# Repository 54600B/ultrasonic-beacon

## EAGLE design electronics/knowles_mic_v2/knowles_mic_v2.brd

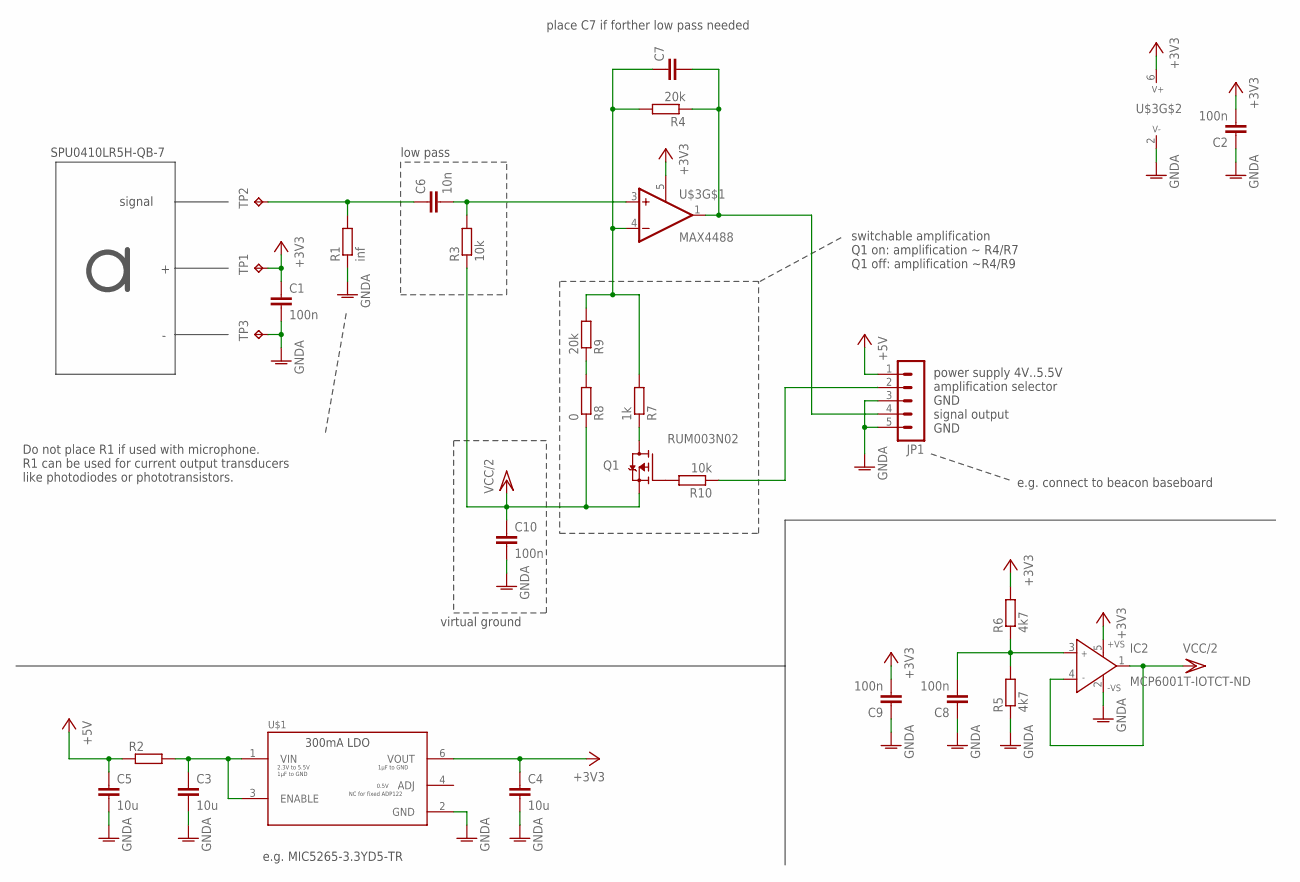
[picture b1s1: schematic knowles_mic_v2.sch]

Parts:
C1, C2, C8, C9, C10: 100n; C0603
C3, C4, C5: 10u; C0805
C6: 10n; C0603
C7: C-EUC0603; C0603
IC2: MCP6001T-IOTCT-ND; SOT23-5
JP1: PSS_5G; 22-23-2051
Q1: RUM003N02; SC75_INFINEON
R1: inf; R0603
R2: R-EU_R0603; R0603
R3, R10: 10k; R0603
R4, R9: 20k; R0603
R5, R6: 4k7; R0603
R7: 1k; R0603
R8: 0; R0603
TP1, TP2, TP3: TPTP06R; TP06R
U$1: ADP123; TSOT23-6
U$3: MAX4488; TSOT23-6

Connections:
+3V3: C1.1, C2.2, C4.1, C9.2, IC2.5 (+VS), R6.2, TP1.TP, U$1.6 (VOUT), U$3.5 (EN), U$3.6 (V+)
+5V: C5.1, JP1.1, R2.1
GNDA: C1.2, C2.1, C3.2, C4.2, C5.2, C8.1, C9.1, C10.2, IC2.2 (-VS), JP1.3, JP1.5, R1.1, R5.1, TP3.TP, U$1.2 (GND), U$3.2 (V-)
unnamed: C8.2, IC2.3 (IN+), R5.2, R6.1
unnamed: R8.2, R9.1
unnamed: C3.1, R2.2, U$1.1 (VIN), U$1.3 (ENABLE)
unnamed: JP1.2, R10.1
unnamed: Q1.1 (G), R10.2
unnamed: Q1.2 (D), R7.1
unnamed: C6.1, R1.2, TP2.TP
unnamed: C6.2, R3.2, U$3.3 (+IN)
unnamed: C7.2, JP1.4, R4.1, U$3.1 (OUT)
unnamed: C7.1, R4.2, R7.2, R9.2, U$3.4 (-IN)
VCC/2: C10.1, IC2.1 (OUT), IC2.4 (IN-), Q1.3 (S), R3.1, R8.1

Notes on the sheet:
e.g. MIC5265-3.3YD5-TR
signal
SPU0410LR5H-QB-7
Do not place R1 if used with microphone. R1 can be used for current output transducers like photodiodes or phototransistors.
low pass
place C7 if forther low pass needed
virtual ground
switchable amplification Q1 on: amplification ~ R4/R7 Q1 off: amplification ~R4/R9
power supply 4V..5.5V amplification selector GND signal output GND
e.g. connect to beacon baseboard

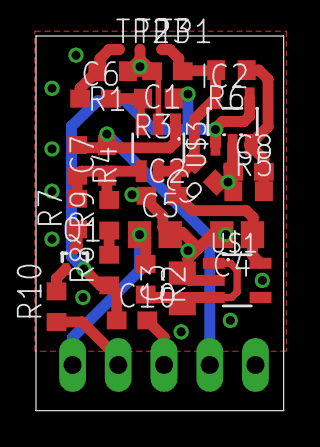
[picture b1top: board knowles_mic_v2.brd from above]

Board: 2 copper layers, 13.8 x 20.8 mm, 28 parts (1 on the bottom side), 14 nets.

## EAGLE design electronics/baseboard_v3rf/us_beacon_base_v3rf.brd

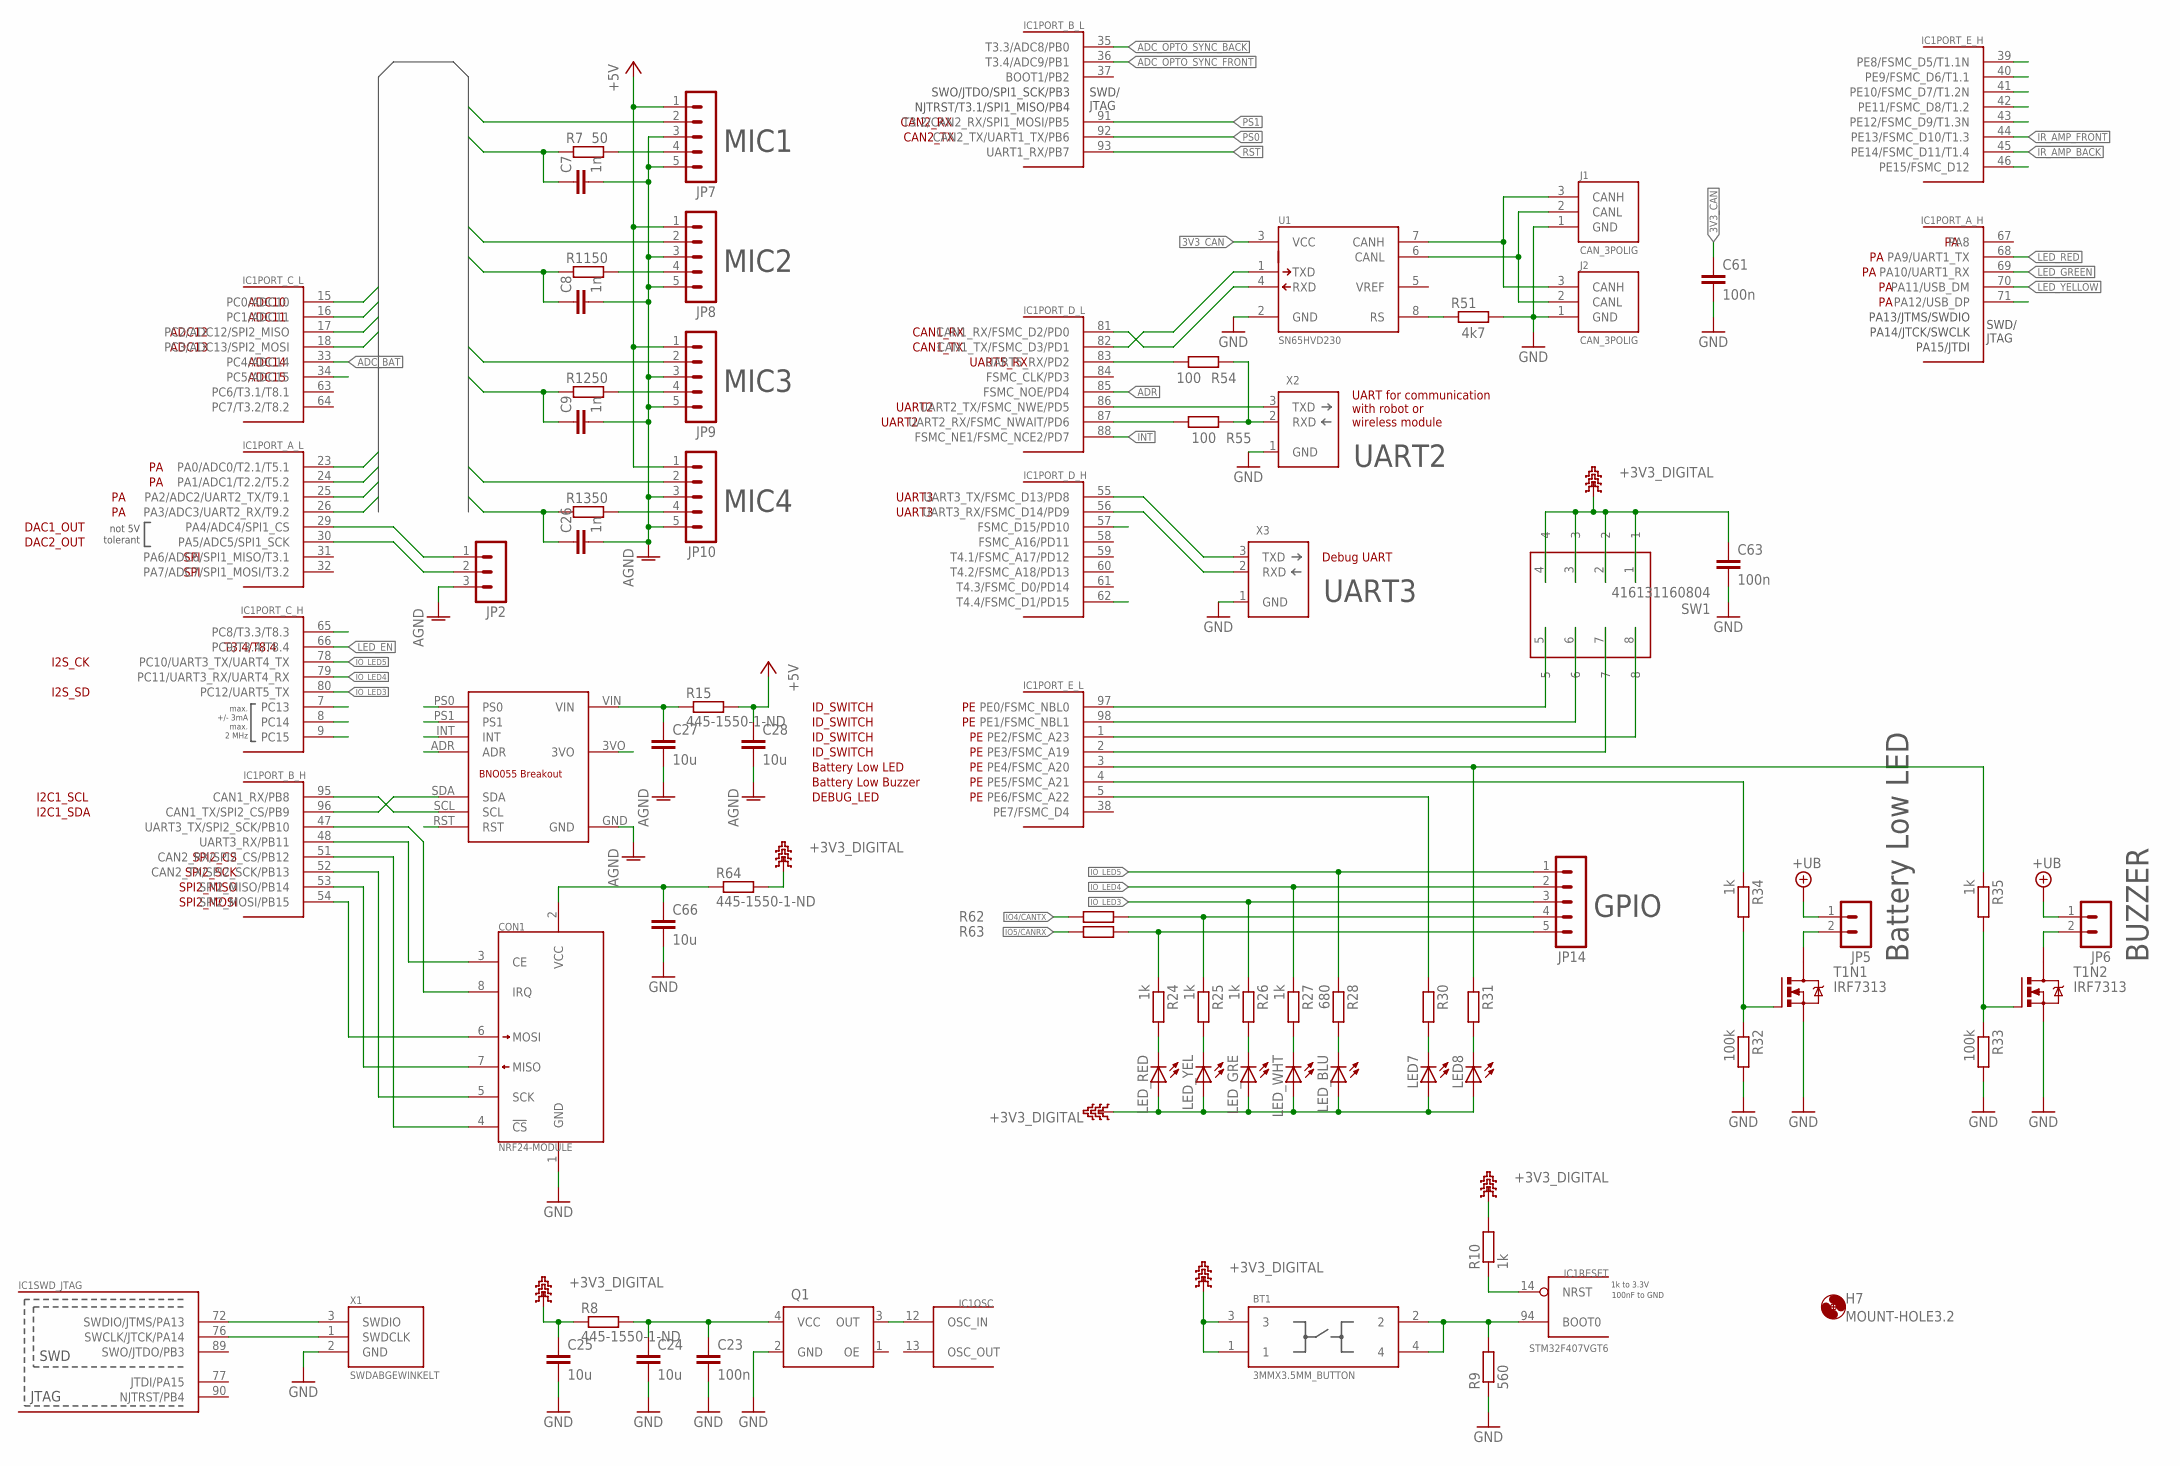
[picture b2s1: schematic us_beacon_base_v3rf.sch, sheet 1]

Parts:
BT1: 3MMX3.5MM_BUTTON
C7, C8, C9, C26: 1n; C0603
C23, C61, C63: 100n; C0603
C24, C25, C27, C28, C66: 10u; C0805
CON1: NRF24-MODULE
H7: MOUNT-HOLE3.2; 3,2
IC1: STM32F407VGT6; TQFP100
J1, J2: CAN_3POLIG; 7395-03
JP2: PSS_3G; 22-23-2031
JP5, JP6: PSS_2G; 22-23-2021
JP7, JP8, JP9, JP10, JP14: PSS_5G; 22-23-2051
LED7, LED8: LEDCHIP-LED0603; CHIP-LED0603
LED_BLU: LEDCHIP-LED0603; CHIP-LED0603
LED_GRE: LEDCHIP-LED0603; CHIP-LED0603
LED_RED: LEDCHIP-LED0603; CHIP-LED0603
LED_WHT: LEDCHIP-LED0603; CHIP-LED0603
LED_YEL: LEDCHIP-LED0603; CHIP-LED0603
Q1: XO53
R7, R11, R12, R13: 50; R0603
R8, R15, R64: 445-1550-1-ND; R0603
R9: 560; R0603
R10, R24, R25, R26, R27, R34, R35: 1k; R0603
R28: 680; R0603
R30, R31, R62, R63: R-EU_R0603; R0603
R32, R33: 100k; R0603
R51: 4k7; R0603
R54, R55: 100; R0603
SW1: 416131160804
T1: IRF7313; SO08
U1: SN65HVD230; SOIC-8
U$1: BNO055_ADAFRUIT_BREAKOUT; BNO055_BREAKOUT
X1: SWDABGEWINKELT; 7395-03
X2, X3: SERIAL_DEBUG_3PINL; 7395-03

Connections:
3V3_CAN: C61.1, U1.3 (VCC); also elsewhere on the board
+3V3_DIGITAL: BT1.1, BT1.3, C25.1, C63.1, LED7.A, LED8.A, LED_BLU.A, LED_GRE.A, LED_RED.A, LED_WHT.A, LED_YEL.A, R8.1, R10.2, R64.2, SW1.1, SW1.2, SW1.3, SW1.4; also elsewhere on the board
+5V: C28.1, JP7.1, JP8.1, JP9.1, JP10.1, R15.2; also elsewhere on the board
+UB: JP5.1, JP6.1; also elsewhere on the board
ADC_BAT: IC1.33 (PC4/ADC14); also elsewhere on the board
ADC_OPTO_SYNC_BACK: IC1.35 (T3.3/ADC8/PB0); also elsewhere on the board
ADC_OPTO_SYNC_FRONT: IC1.36 (T3.4/ADC9/PB1); also elsewhere on the board
ADR: IC1.85 (FSMC_NOE/PD4), U$1.ADR
AMP1: IC1.23 (PA0/ADC0/T2.1/T5.1), JP7.2
AMP2: IC1.24 (PA1/ADC1/T2.2/T5.2), JP8.2
AMP3: IC1.25 (PA2/ADC2/UART2_TX/T9.1), JP9.2
AMP4: IC1.26 (PA3/ADC3/UART2_RX/T9.2), JP10.2
DAC1/I2S1_WS: IC1.29 (PA4/ADC4/SPI1_CS), JP2.1
DAC2/SPI1_SCK: IC1.30 (PA5/ADC5/SPI1_SCK), JP2.2
GND: C7.2, C8.2, C9.2, C23.2, C24.2, C25.2, C26.2, C27.2, C28.2, C61.2, C63.2, C66.2, CON1.1 (GND), J1.1 (GND), J2.1 (GND), JP2.3, JP7.3, JP7.5, JP8.3, JP8.5, JP9.3, JP9.5, JP10.3, JP10.5, Q1.2 (GND), R9.1, R32.2, R33.2, R51.2, T1.1 (S), T1.3 (S), U1.2 (GND), U$1.GND, X1.2 (GND), X2.1 (GND), X3.1 (GND); also elsewhere on the board
INT: IC1.88 (FSMC_NE1/FSMC_NCE2/PD7), U$1.INT
IO4: JP14.4, R25.1, R62.2
IO4/CANTX: IC1.82 (CAN1_TX/FSMC_D3/PD1), R62.1, U1.1 (TXD)
IO5: JP14.5, R24.1, R63.2
IO5/CANRX: IC1.81 (CAN1_RX/FSMC_D2/PD0), R63.1, U1.4 (RXD)
IO_LED3: IC1.80 (PC12/UART5_TX), JP14.3, R26.1
IO_LED4: IC1.79 (PC11/UART3_RX/UART4_RX), JP14.2, R27.1
IO_LED5: IC1.78 (PC10/UART3_TX/UART4_TX), JP14.1, R28.1
IR_AMP_BACK: IC1.45 (PE14/FSMC_D11/T1.4); also elsewhere on the board
IR_AMP_FRONT: IC1.44 (PE13/FSMC_D10/T1.3); also elsewhere on the board
LED_EN: IC1.66 (PC9/T3.4/T8.4); also elsewhere on the board
LED_GREEN: IC1.69 (PA10/UART1_RX); also elsewhere on the board
LED_RED: IC1.68 (PA9/UART1_TX); also elsewhere on the board
LED_YELLOW: IC1.70 (PA11/USB_DM); also elsewhere on the board
MIC1: C7.1, IC1.15 (PC0/ADC10), R7.1
MIC2: C8.1, IC1.16 (PC1/ADC11), R11.1
MIC3: C9.1, IC1.17 (PC2/ADC12/SPI2_MISO), R12.1
MIC4: C26.1, IC1.18 (PC3/ADC13/SPI2_MOSI), R13.1
unnamed: IC1.72 (SWDIO/JTMS/PA13), X1.3 (SWDIO)
unnamed: IC1.76 (SWCLK/JTCK/PA14), X1.1 (SWDCLK)
unnamed: JP7.4, R7.2
unnamed: IC1.12 (OSC_IN), Q1.3 (OUT)
unnamed: C23.1, C24.1, Q1.4 (VCC), R8.2
unnamed: JP9.4, R12.2
unnamed: IC1.14 (NRST), R10.1
unnamed: JP8.4, R11.2
unnamed: JP10.4, R13.2
unnamed: BT1.2, BT1.4, IC1.94 (BOOT0), R9.2
unnamed: IC1.83 (UART5_RX/PD2), R54.1
unnamed: C27.1, R15.1, U$1.VIN
unnamed: R54.2, R55.2, X2.2 (RXD)
unnamed: IC1.95 (CAN1_RX/PB8), U$1.SCL
unnamed: IC1.96 (CAN1_TX/SPI2_CS/PB9), U$1.SDA
unnamed: IC1.86 (UART2_TX/FSMC_NWE/PD5), X2.3 (TXD)
unnamed: IC1.87 (UART2_RX/FSMC_NWAIT/PD6), R55.1
unnamed: IC1.55 (UART3_TX/FSMC_D13/PD8), X3.3 (TXD)
unnamed: IC1.56 (UART3_RX/FSMC_D14/PD9), X3.2 (RXD)
unnamed: LED_RED.C, R24.2
unnamed: LED_YEL.C, R25.2
unnamed: LED_GRE.C, R26.2
unnamed: LED_WHT.C, R27.2
unnamed: LED_BLU.C, R28.2
unnamed: LED7.C, R30.2
unnamed: LED8.C, R31.2
unnamed: IC1.3 (PE4/FSMC_A20), R31.1, R35.1
unnamed: IC1.5 (PE6/FSMC_A22), R30.1
unnamed: R32.1, R34.2, T1.2 (G)
unnamed: R33.1, R35.2, T1.4 (G)
unnamed: JP5.2, T1.7 (D)
unnamed: IC1.4 (PE5/FSMC_A21), R34.1
unnamed: JP6.2, T1.5 (D)
unnamed: IC1.2 (PE3/FSMC_A19), SW1.7
unnamed: IC1.97 (PE0/FSMC_NBL0), SW1.5
unnamed: IC1.98 (PE1/FSMC_NBL1), SW1.6
unnamed: IC1.1 (PE2/FSMC_A23), SW1.8
unnamed: R51.1, U1.8 (RS)
unnamed: J1.3 (CANH), J2.3 (CANH), U1.7 (CANH)
unnamed: J1.2 (CANL), J2.2 (CANL), U1.6 (CANL)
unnamed: CON1.4 (!CS), IC1.51 (CAN2_RX/SPI2_CS/PB12)
unnamed: CON1.5 (SCK), IC1.52 (CAN2_TX/SPI2_SCK/PB13)
unnamed: CON1.7 (MISO), IC1.53 (SPI2_MISO/PB14)
unnamed: CON1.6 (MOSI), IC1.54 (SPI2_MOSI/PB15)
unnamed: CON1.3 (CE), IC1.48 (UART3_RX/PB11)
unnamed: CON1.8 (IRQ), IC1.47 (UART3_TX/SPI2_SCK/PB10)
unnamed: C66.1, CON1.2 (VCC), R64.1
PS0: IC1.92 (CAN2_TX/UART1_TX/PB6), U$1.PS0
PS1: IC1.91 (T3.2/CAN2_RX/SPI1_MOSI/PB5), U$1.PS1
RST: IC1.93 (UART1_RX/PB7), U$1.RST
VBAT: IC1.6 (VBAT)

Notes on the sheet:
ADC11
SPI2_CS
SPI2_SCK
CAN1_RX
CAN1_TX
SPI2_MOSI
SPI2_MISO
ADC10
ADC14
ADC15
UART2
UART3
DAC1_OUT
DAC2_OUT
I2S_CK
I2S_SD
SPI
CAN2_RX
CAN2_TX
I2C1_SCL
I2C1_SDA
ADC12
ADC13
ID_SWITCH
Battery Low LED
Battery Low Buzzer
DEBUG_LED
MIC1
MIC2
MIC3
MIC4
GPIO
BUZZER
Debug UART
UART for communication with robot or wireless module
T3.4/T8.4
UART5_RX

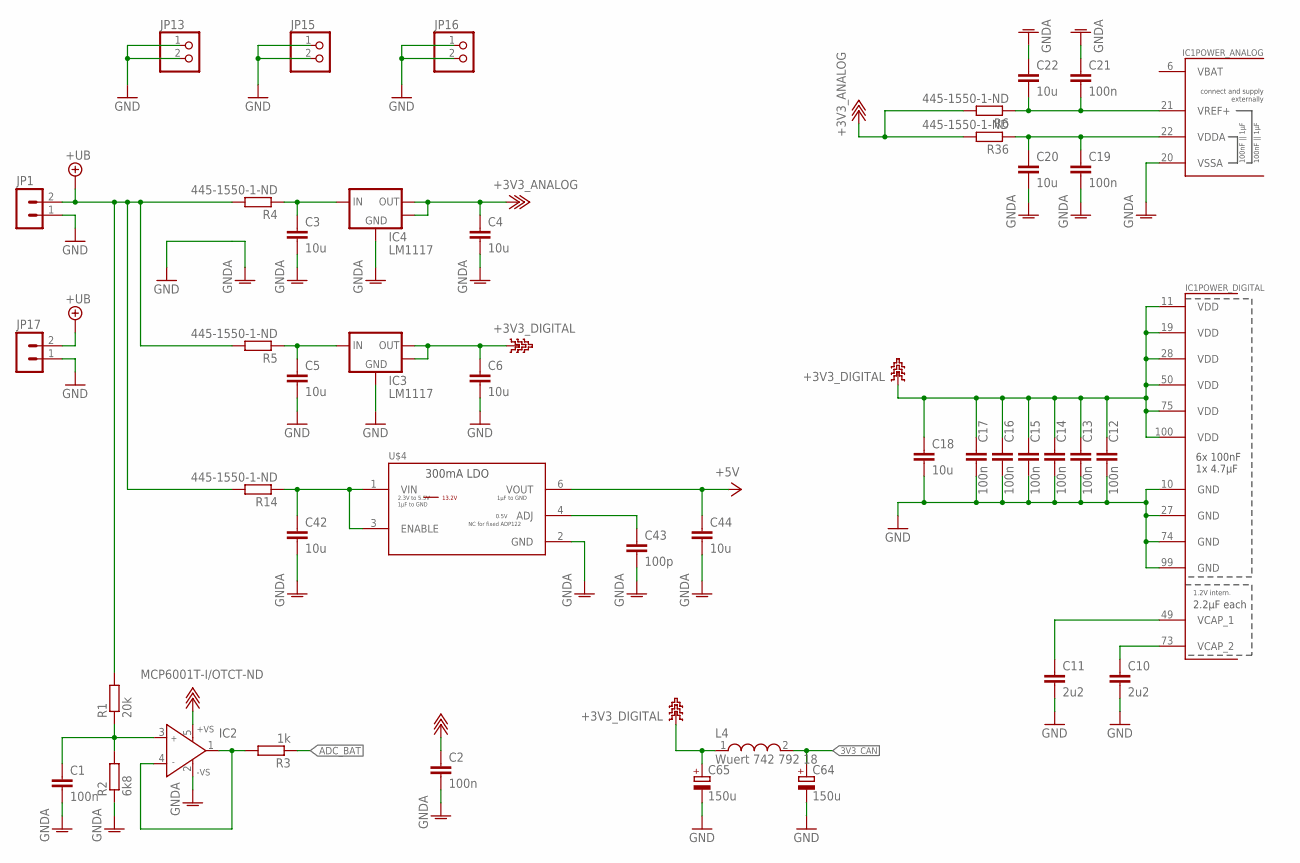
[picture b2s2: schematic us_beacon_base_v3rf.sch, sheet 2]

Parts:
C1, C2, C12, C13, C14, C15, C16, C17, C19, C21: 100n; C0603
C3, C4, C5, C6, C18, C20, C22, C42, C44: 10u; C0805
C10, C11: 2u2; C0805
C43: 100p; C0603
C64, C65: 150u; E3,5-8
IC1: STM32F407VGT6; TQFP100
IC2: MCP6001T-I/OTCT-ND; SOT23-5
IC3, IC4: LM1117; SOT223
JP1, JP17: PSS_2G; 22-23-2021
JP13, JP15, JP16: PINHD-1X2; 1X02
L4: Wuert 742 792 18; WE-CBF_1206(W=5.2)
R1: 20k; R0603
R2: 6k8; R0603
R3: 1k; R0603
R4, R5, R6, R14, R36: 445-1550-1-ND; R0603
U$4: AP2210K-5.0; TSOT23-6

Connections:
3V3_CAN: C64.+, L4.2; also elsewhere on the board
+3V3_ANALOG: C2.1, C4.1, IC2.5 (+VS), IC4.2 (OUT), IC4.4 (OUT), R6.2, R36.2; also elsewhere on the board
+3V3_DIGITAL: C6.1, C12.1, C13.1, C14.1, C15.1, C16.1, C17.1, C18.1, C65.+, IC1.11 (VDD), IC1.19 (VDD), IC1.28 (VDD), IC1.50 (VDD), IC1.75 (VDD), IC1.100 (VDD), IC3.2 (OUT), IC3.4 (OUT), L4.1; also elsewhere on the board
+5V: C44.1, U$4.6 (VOUT); also elsewhere on the board
+UB: JP1.2, JP17.2, R1.2, R4.2, R5.2, R14.2; also elsewhere on the board
ADC_BAT: R3.1; also elsewhere on the board
GND: C1.2, C2.2, C3.2, C4.2, C5.2, C6.2, C10.2, C11.2, C12.2, C13.2, C14.2, C15.2, C16.2, C17.2, C18.2, C19.2, C20.2, C21.1, C22.1, C42.2, C43.2, C44.2, C64.-, C65.-, IC1.10 (GND), IC1.20 (VSSA), IC1.27 (GND), IC1.74 (GND), IC1.99 (GND), IC2.2 (-VS), IC3.1 (GND), IC4.1 (GND), JP1.1, JP13.1, JP13.2, JP15.1, JP15.2, JP16.1, JP16.2, JP17.1, R2.1, U$4.2 (GND); also elsewhere on the board
unnamed: IC2.1 (OUT), IC2.4 (IN-), R3.2
unnamed: C1.1, IC2.3 (IN+), R1.1, R2.2
unnamed: C42.1, R14.1, U$4.1 (VIN), U$4.3 (ENABLE)
unnamed: C3.1, IC4.3 (IN), R4.1
unnamed: C10.1, IC1.73 (VCAP_2)
unnamed: C5.1, IC3.3 (IN), R5.1
unnamed: C11.1, IC1.49 (VCAP_1)
unnamed: C21.2, C22.2, IC1.21 (VREF+), R6.1
unnamed: C43.1, U$4.4 (ADJ)
unnamed: C19.1, C20.1, IC1.22 (VDDA), R36.1
VBAT: IC1.6 (VBAT)

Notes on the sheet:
13.2V

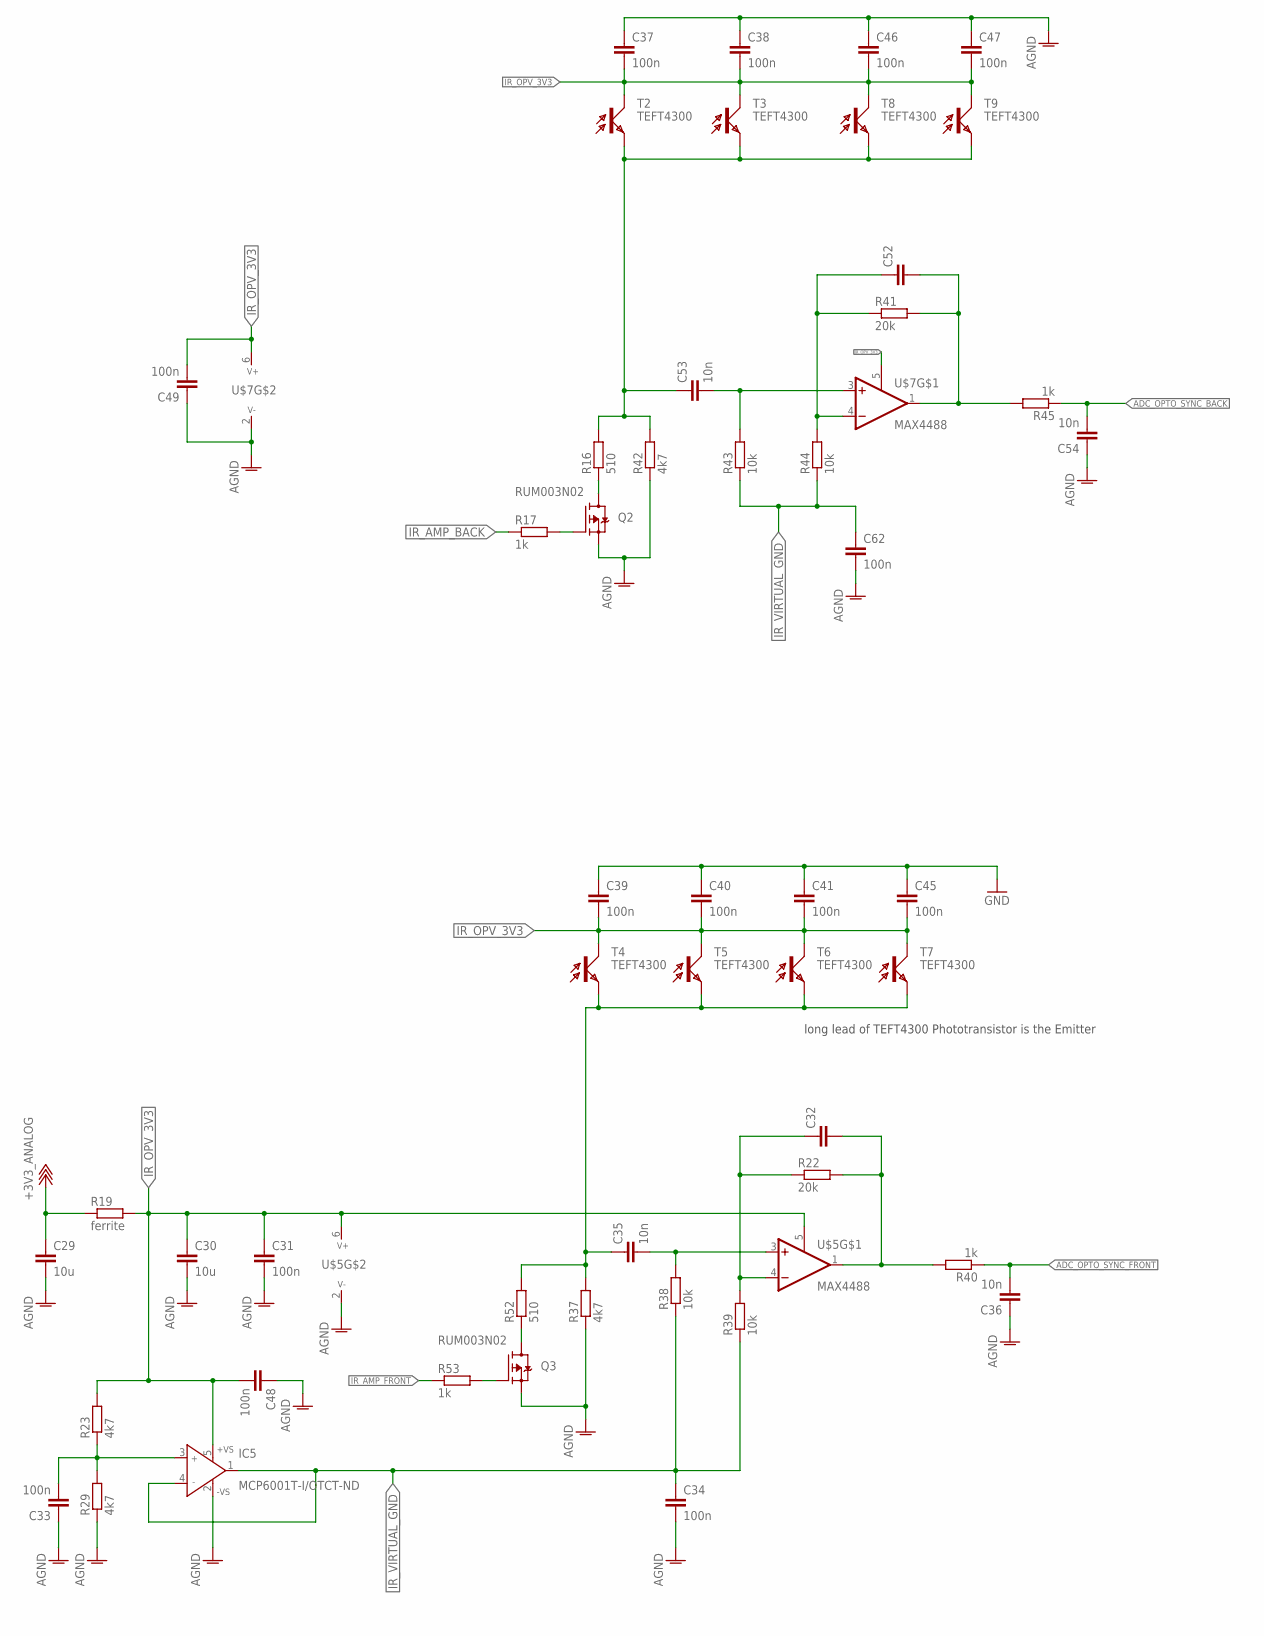
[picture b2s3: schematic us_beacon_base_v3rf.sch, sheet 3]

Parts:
C29, C30: 10u; C0805
C31, C33, C34, C37, C38, C39, C40, C41, C45, C46, C47, C48, C49, C62: 100n; C0603
C32, C52: C-EUC0603; C0603
C35, C36, C53, C54: 10n; C0603
IC5: MCP6001T-I/OTCT-ND; SOT23-5
Q2, Q3: RUM003N02; SC75_INFINEON
R16, R52: 510; R0603
R17, R40, R45, R53: 1k; R0603
R19: ferrite; R0603
R22, R41: 20k; R0603
R23, R29, R37, R42: 4k7; R0603
R38, R39, R43, R44: 10k; R0603
T2, T3, T4, T5, T6, T7, T8, T9: TEFT4300; LPT80A
U$5, U$7: MAX4488; TSOT23-6

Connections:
+3V3_ANALOG: C29.1, R19.1; also elsewhere on the board
ADC_OPTO_SYNC_BACK: C54.2, R45.1; also elsewhere on the board
ADC_OPTO_SYNC_FRONT: C36.2, R40.1; also elsewhere on the board
GND: C29.2, C30.2, C31.2, C33.1, C34.2, C36.1, C37.1, C38.1, C39.1, C40.1, C41.1, C45.1, C46.1, C47.1, C48.1, C49.1, C54.1, C62.2, IC5.2 (-VS), Q2.3 (S), Q3.3 (S), R29.1, R37.1, R42.1, U$5.2 (V-), U$7.2 (V-); also elsewhere on the board
IR_AMP_BACK: R17.1; also elsewhere on the board
IR_AMP_FRONT: R53.1; also elsewhere on the board
IR_OPV_3V3: C30.1, C31.1, C37.2, C38.2, C39.2, C40.2, C41.2, C45.2, C46.2, C47.2, C48.2, C49.2, IC5.5 (+VS), R19.2, R23.2, T2.C, T3.C, T4.C, T5.C, T6.C, T7.C, T8.C, T9.C, U$5.5 (EN), U$5.6 (V+), U$7.5 (EN), U$7.6 (V+)
IR_VIRTUAL_GND: C34.1, C62.1, IC5.1 (OUT), IC5.4 (IN-), R38.1, R39.1, R43.1, R44.1
unnamed: Q2.2 (D), R16.1
unnamed: Q2.1 (G), R17.2
unnamed: C53.1, R16.2, R42.2, T2.E, T3.E, T8.E, T9.E
unnamed: C35.2, R38.2, U$5.3 (+IN)
unnamed: Q3.2 (D), R52.1
unnamed: C32.2, R22.2, R40.2, U$5.1 (OUT)
unnamed: C32.1, R22.1, R39.2, U$5.4 (-IN)
unnamed: Q3.1 (G), R53.2
unnamed: C33.2, IC5.3 (IN+), R23.1, R29.2
unnamed: C52.2, R41.2, R45.2, U$7.1 (OUT)
unnamed: C52.1, R41.1, R44.2, U$7.4 (-IN)
unnamed: C35.1, R37.2, R52.2, T4.E, T5.E, T6.E, T7.E
unnamed: C53.2, R43.2, U$7.3 (+IN)

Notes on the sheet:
long lead of TEFT4300 Phototransistor is the Emitter

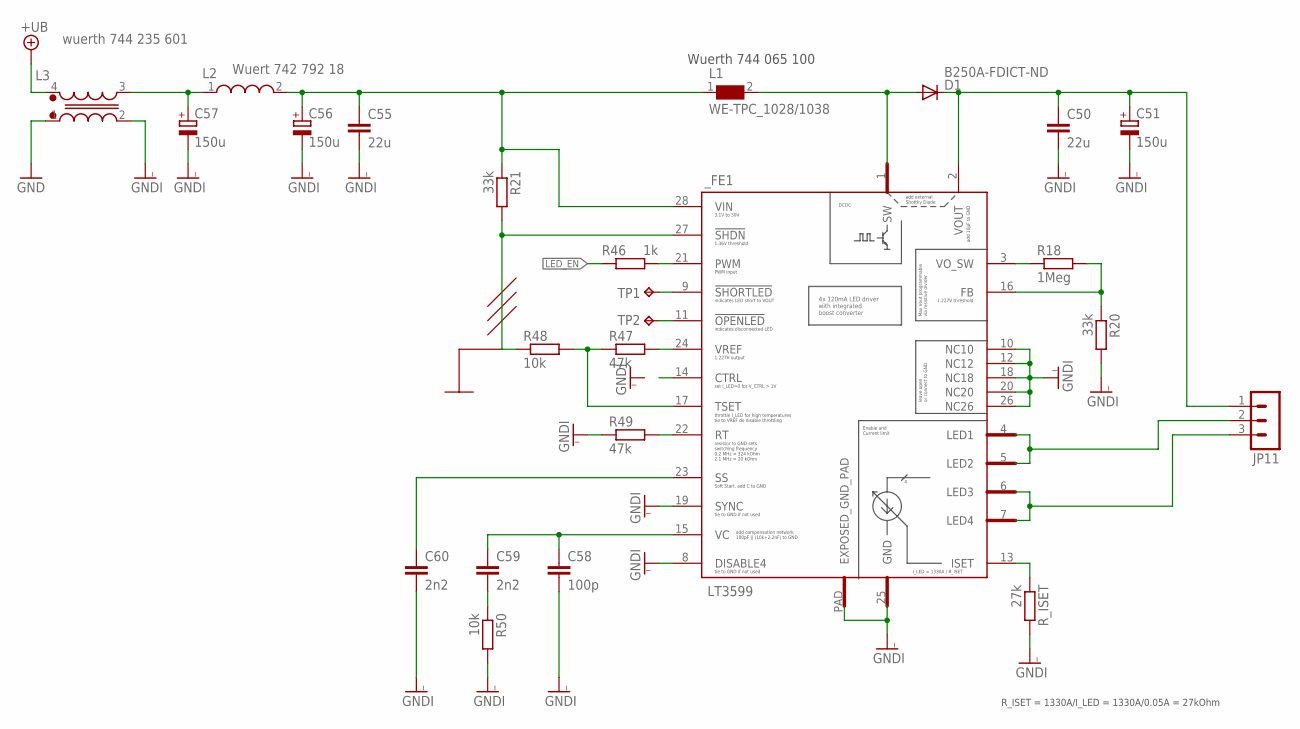
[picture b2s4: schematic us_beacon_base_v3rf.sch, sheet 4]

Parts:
C50, C55: 22u; C1206
C51, C56, C57: 150u; E3,5-8
C58: 100p; C0603
C59, C60: 2n2; C0603
D1: B250A-FDICT-ND; SMB
JP11: PSS_3G; 22-23-2031
L1: WE-TPC_1028/1038
L2: Wuert 742 792 18; WE-CBF_1206(W=5.2)
L3: wuerth 744 235 601; WE-CNSW_1812
R18: 1Meg; R0603
R20, R21: 33k; R0603
R46: 1k; R0603
R47, R49: 47k; R0603
R48, R50: 10k; R0603
R_ISET: 27k; R0603
TP1, TP2: TPTP06R; TP06R
_FE1: LT3599; TSSOP28

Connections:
+UB: L3.4 (1); also elsewhere on the board
DCDC_SW_NODE: D1.A, L1.2, _FE1.1 (SW)
GND: L3.1 (4); also elsewhere on the board
GNDI: C50.2, C51.-, C55.2, C56.-, C57.-, C58.2, C60.2, L3.2 (3), R20.2, R49.1, R50.2, R_ISET.2, _FE1.8 (DISABLE4), _FE1.10 (NC10), _FE1.12 (NC12), _FE1.18 (NC18), _FE1.19 (SYNC), _FE1.20 (NC20), _FE1.25 (GND), _FE1.26 (NC26), _FE1.PAD (EXPOSED_GND_PAD)
LED_EN: R46.1; also elsewhere on the board
unnamed: R46.2, _FE1.21 (PWM)
unnamed: C57.+, L2.1, L3.3 (2)
unnamed: C58.1, C59.1, _FE1.15 (VC)
unnamed: C50.1, C51.+, D1.C, JP11.1, _FE1.2 (VOUT)
unnamed: JP11.2, _FE1.4 (LED1), _FE1.5 (LED2)
unnamed: JP11.3, _FE1.6 (LED3), _FE1.7 (LED4)
unnamed: R18.2, R20.1, _FE1.16 (FB)
unnamed: R18.1, _FE1.3 (VO_SW)
unnamed: TP1.TP, _FE1.9 (!SHORTLED)
unnamed: TP2.TP, _FE1.11 (!OPENLED)
unnamed: R47.1, R48.2, _FE1.17 (TSET)
unnamed: R47.2, _FE1.24 (VREF)
unnamed: R21.2, R48.1, _FE1.27 (!SHDN)
unnamed: C55.1, C56.+, L1.1, L2.2, R21.1, _FE1.28 (VIN)
unnamed: R49.2, _FE1.22 (RT)
unnamed: C60.1, _FE1.23 (SS)
unnamed: C59.2, R50.1
unnamed: R_ISET.1, _FE1.13 (ISET)

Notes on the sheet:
R_ISET = 1330A/I_LED = 1330A/0.05A = 27kOhm
Wuerth 744 065 100

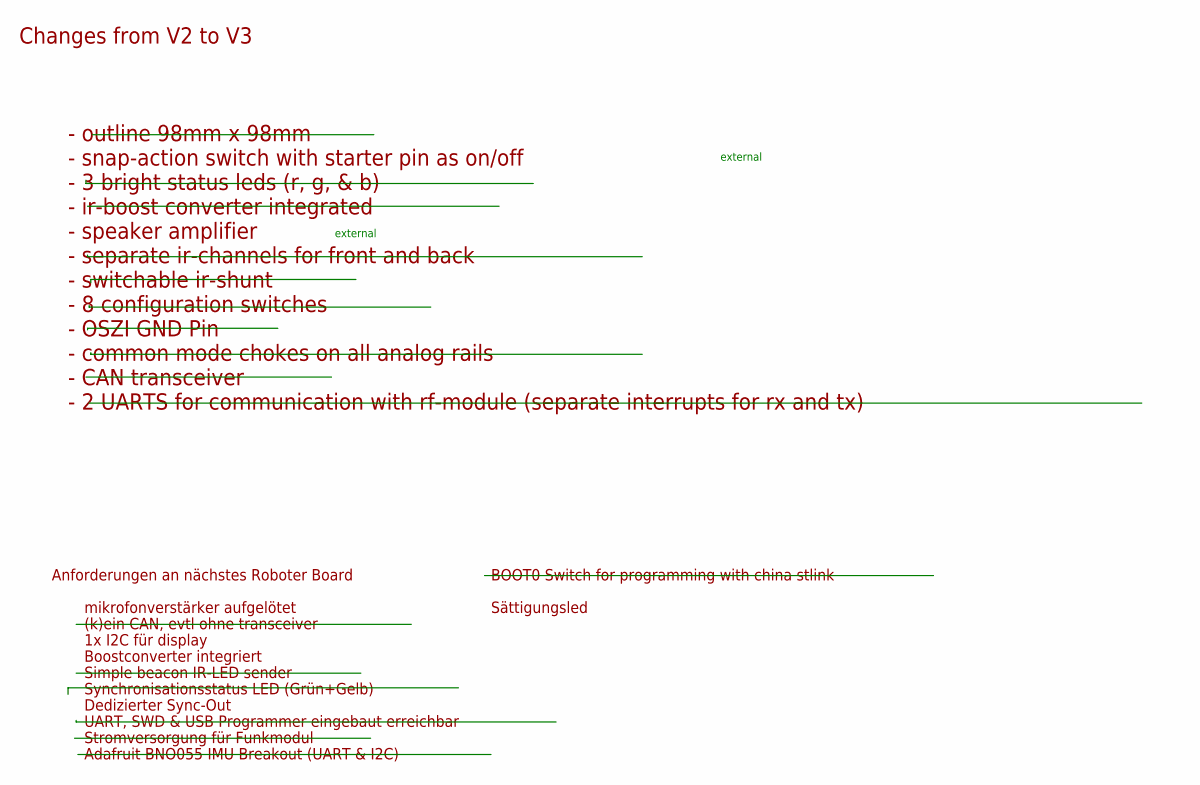
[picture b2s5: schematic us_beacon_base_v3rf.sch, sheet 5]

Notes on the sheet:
- outline 98mm x 98mm - snap-action switch with starter pin as on/off - 3 bright status leds (r, g, & b) - ir-boost converter integrated - speaker amplifier - separate ir-channels for front and back - switchable ir-shunt - 8 configuration switches - OSZI GND Pin - common mode chokes on all analog r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
Changes from V2 to V3
BOOT0 Switch for programming with china stlink
Sättigungsled
Anforderungen an nächstes Roboter Board
mikrofonverstärker aufgelötet
(k)ein CAN, evtl ohne transceiver
1x I2C für display
Boostconverter integriert
Simple beacon IR-LED sender
Synchronisationsstatus LED (Grün+Gelb)
Dedizierter Sync-Out
UART, SWD & USB Programmer eingebaut erreichbar
Stromversorgung für Funkmodul
Adafruit BNO055 IMU Breakout (UART & I2C)
external

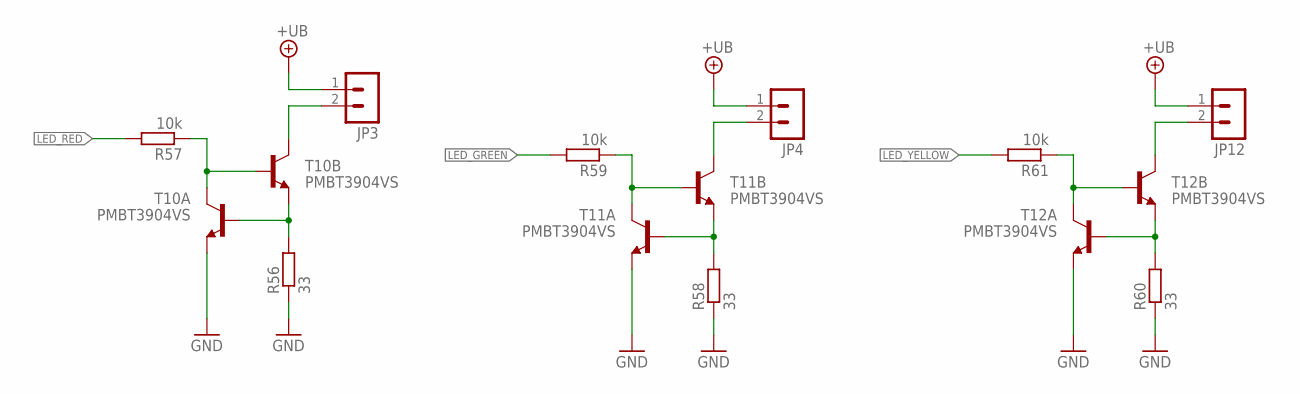
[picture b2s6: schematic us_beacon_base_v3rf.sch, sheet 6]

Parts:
JP3, JP4, JP12: PSS_2G; 22-23-2021
R56, R58, R60: 33; R0603
R57, R59, R61: 10k; R0603
T10, T11, T12: PMBT3904VS; SOT563

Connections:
+UB: JP3.1, JP4.1, JP12.1; also elsewhere on the board
GND: R56.1, R58.1, R60.1, T10.1 (E), T11.1 (E), T12.1 (E); also elsewhere on the board
LED_GREEN: R59.2; also elsewhere on the board
LED_RED: R57.2; also elsewhere on the board
LED_YELLOW: R61.2; also elsewhere on the board
unnamed: R56.2, T10.2 (B), T10.4 (E)
unnamed: R57.1, T10.5 (B), T10.6 (C)
unnamed: JP3.2, T10.3 (C)
unnamed: R58.2, T11.2 (B), T11.4 (E)
unnamed: R59.1, T11.5 (B), T11.6 (C)
unnamed: JP4.2, T11.3 (C)
unnamed: R60.2, T12.2 (B), T12.4 (E)
unnamed: R61.1, T12.5 (B), T12.6 (C)
unnamed: JP12.2, T12.3 (C)

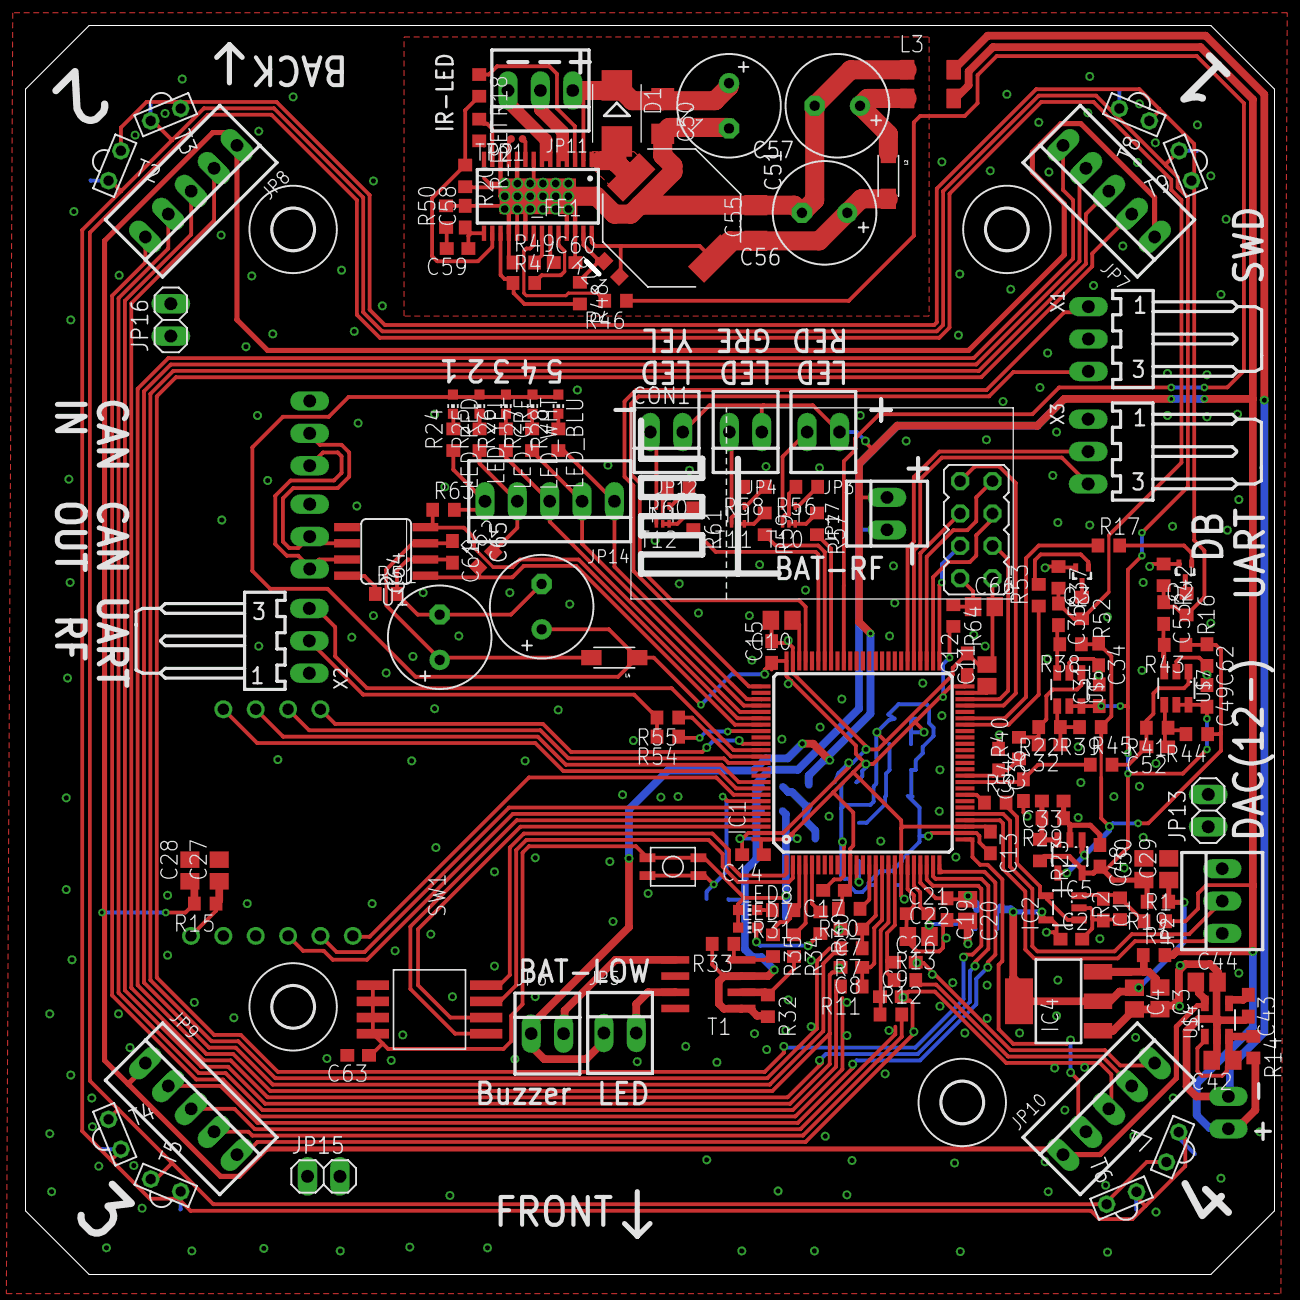
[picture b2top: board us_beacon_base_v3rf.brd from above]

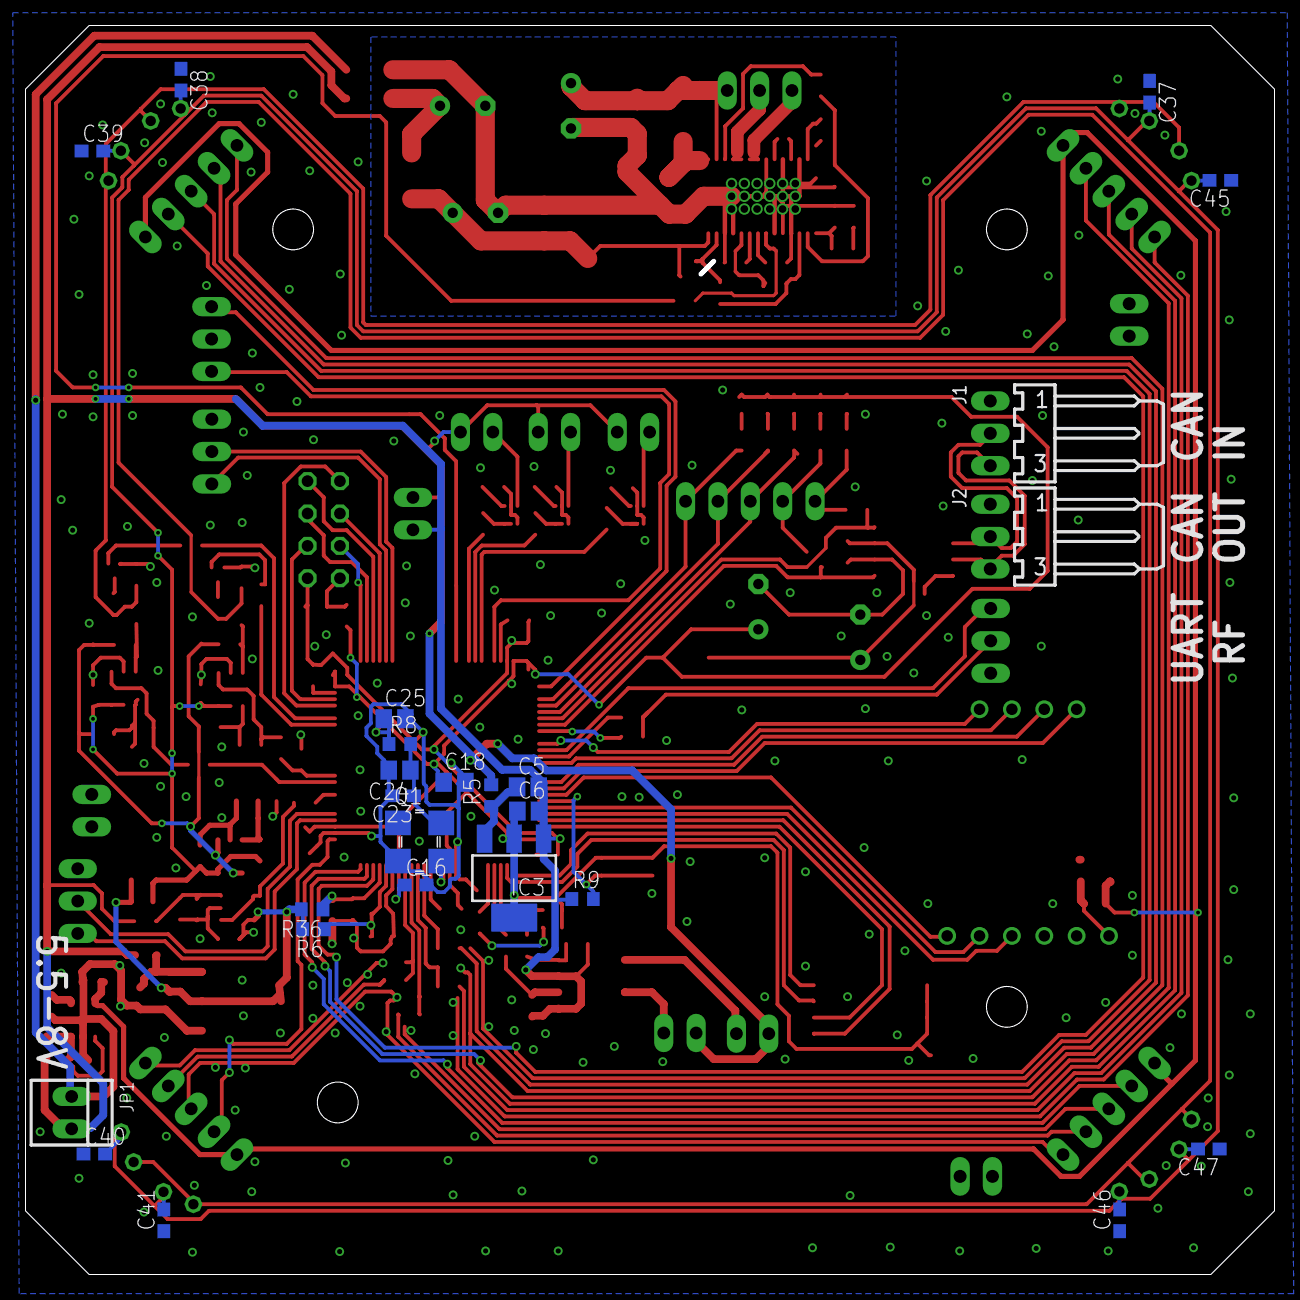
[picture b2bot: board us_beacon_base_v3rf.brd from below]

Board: 2 copper layers, 97.6 x 97.6 mm, 200 parts (25 on the bottom side), 138 nets.

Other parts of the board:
H5, H6, H8: MOUNT-HOLE3.2; 3,2

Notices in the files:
software/beacon-uC/US_Beacon_V3/Src/main.c:
Copyright (c) 2018 STMicroelectronics International N.V.
All rights reserved.
(C) COPYRIGHT STMicroelectronics *****END OF FILE
parts and their libraries:
Wurth_Elektronik_Passive_rev15b: Copyright: Würth Elektronik
